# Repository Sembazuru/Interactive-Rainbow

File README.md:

# Interactive-Rainbow
Interactive Rainbow panel of RGB LEDs for the Barrel of Makers windmill project.

This is the state as first built as the Trippy-RGB wall with point-to-point wiring.
Any updates or changes to the first build should be documented here.

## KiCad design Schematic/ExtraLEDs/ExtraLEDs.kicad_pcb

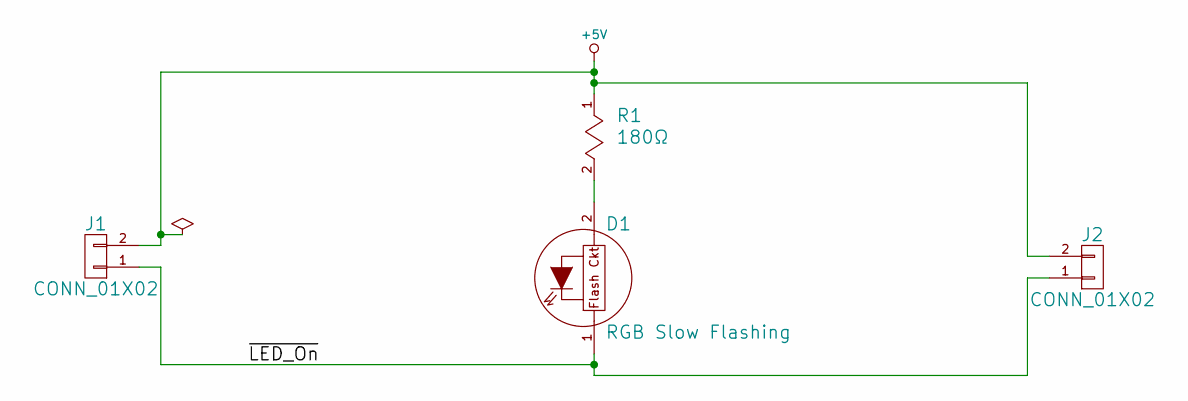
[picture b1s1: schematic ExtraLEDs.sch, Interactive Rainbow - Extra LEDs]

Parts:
D1: RGB Slow Flashing; LEDRD254W50D500H960P; MfgPart ADA679
J1, J2: CONN_01X02; HDRV2W64P254_1X2_508X254X1016A
R1: 180Ω; RESAD1016W56L681D259

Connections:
+5V: J1.2, J2.2, R1.1
/~LED_On: D1.1 (K), J1.1, J2.1
unnamed: D1.2 (A), R1.2

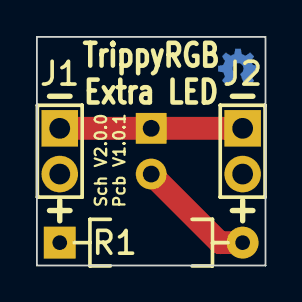
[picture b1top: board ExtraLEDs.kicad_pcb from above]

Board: 2 copper layers, 12.7 x 12.7 mm, 4 parts (1 on the bottom side), 3 nets.

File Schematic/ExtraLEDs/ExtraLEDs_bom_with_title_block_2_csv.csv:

Source,C:\Users\Chris\Google Drive\Barrel of Makers\Windmill LED panel\Schematic\ExtraLEDs\ExtraLEDs.sch
Kicad Rev,Eeschema 4.0.4-stable
Generated Date,2016-10-07 00:31:17

Title,Interactive Rainbow
Company,Sembazuru Circuit (for Barrel of Makers)
Revision,2.0.0
Date Issue,2016-05-27
Comment,2.0.0 Split schematic up for 4 individual PWB designs

Reference,Value,CommonPartLibrary,MFN,MFP,Package ID,S1PN,S1PL,S2PN,S2PL,Characteristics,Description,Critical,Source,Notes,Mfg,MfgPart,Library,Library Ref
D1,RGB Slow Flashing,CPL-LED-RGB-CYCLING-SLOW*,AdaFruit,679,JEDEC footprint name,ADA679,https://octopart.com/search?q=ADA679,679,https://www.adafruit.com/product/679,Diffused 5mm Slow Fade Flashing RGB LED - 10 pack,Self-cycling LED, slow speed, 10pk,Y,SPEC,Explain critera for "ANY" Source,AdaFruit,ADA679,NewUnsorted,LED_Flashing
R1,180Ω,CPL-RES-THT-180-0.25W*,Yageo,MFR-25FBF52-180R,JEDEC footprint name,MFR-25FBF52-180R,https://octopart.com/search?q=MFR-25FBF52-180R,603-MFR-25FBF52-180R,http://www.mouser.com/search/ProductDetail.aspx?R=0virtualke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,180Ω,Current limiting resistor for LED.,N,ANY,Any tolerance THT 180Ω 1/4W or 1/8W resistor will do.,,,NewUnsorted,RES
J1,CONN_01X02,CPL-,Manufacturer Name,Manufacturer Part Number,JEDEC footprint name,Source1 Part Number,Source1 Product Link,Source2 Part Number,Source2 Product Link,Voltage / Current / Tolerance / Ect specs,Footprint for 25mil square pin header. Use header or direct solder wires.,Y / N,ANY / SPEC,Explain critera for "ANY" Source,,,NewUnsorted,CONN_01X02
J2,CONN_01X02,CPL-,Manufacturer Name,Manufacturer Part Number,JEDEC footprint name,Source1 Part Number,Source1 Product Link,Source2 Part Number,Source2 Product Link,Voltage / Current / Tolerance / Ect specs,Footprint for 25mil square pin header. Use header or direct solder wires.,Y / N,ANY / SPEC,Explain critera for "ANY" Source,,,NewUnsorted,CONN_01X02

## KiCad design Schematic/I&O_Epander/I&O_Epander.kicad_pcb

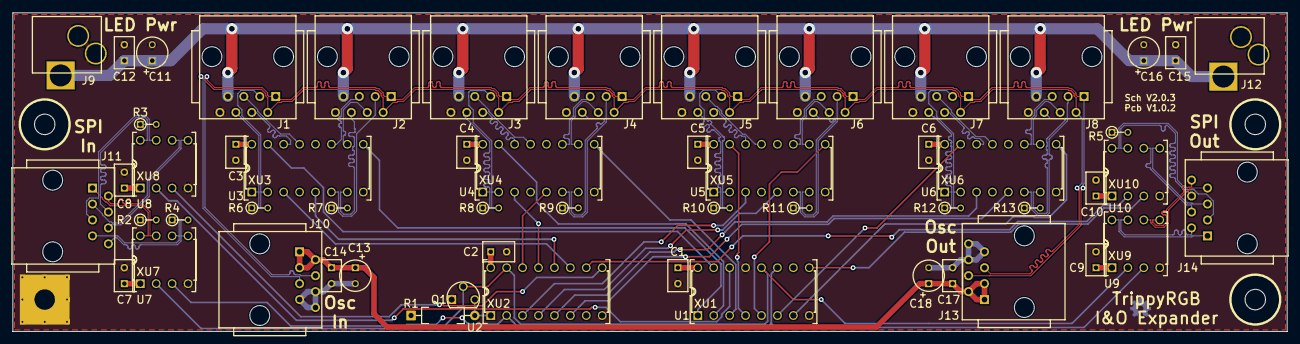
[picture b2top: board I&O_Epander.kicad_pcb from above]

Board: 2 copper layers, 203.2 x 50.8 mm, 70 parts (0 on the bottom side), 76 nets.

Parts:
C1, C2, C3, C4, C5, C6, C7, C8, C9, C10, C12, C14, C15, C17: 0.1µF; CAPRR254W51L508T318H660P
C11, C13, C16, C18: 10µF; CAPPRD254W50D500H850
J1, J2, J3, J4, J5, J6, J7, J8, J10, J11, J13, J14: RJ45-Unshielded; WURTH_615008144221
J9, J12: KLDVHCX-0202-A; KYCON_KLDVHCX-0202-x_CirHole
MH1: #4 PTH; MTGP794H326V8P
MH2, MH3, MH4: #4 NPTH; MTGNP794H326Z794P
Q1: VN3205; TO92184P520H734-3
R1: 1kΩ; RESAD1016W56L681D259
R2, R3, R4, R5, R6, R7, R8, R9, R10, R11, R12, R13: 100Ω; RESADV254W45L350D185
U1: 74HC595; DIPS762W45P254L2019H508Q16
U2: 74HC165; DIPS762W45P254L2019H508Q16
U3, U4, U5, U6: 75C1168; DIPS762W45P254L2019H508Q16
U7: uA9637AC; DIPS762W45P254L1003H508Q8
U8, U10: DS8921; DIPS762W45P254L1003H508Q8
U9: uA9638C; DIPS762W45P254L1003H508Q8
XU1, XU2, XU3, XU4, XU5, XU6: IC_Socket16; DIPfS794W45P254L1969H508Q16
XU7, XU8, XU9, XU10: IC_Socket08; DIPfS762W45P254L1016H508Q8

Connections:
+5V(1): C1.1, C2.1, C3.1, C4.1, C5.1, C6.1, C7.1, C8.1, C9.1, C10.1, C13.1, C14.1, C17.1, C18.1, J10.1, J10.2, J10.3, J13.1, J13.2, J13.3, R1.1, U1.10, U1.16, U2.16, U3.4, U3.12, U3.16, U4.4, U4.12, U4.16, U5.4, U5.12, U5.16, U6.4, U6.12, U6.16, U7.1, U8.1, U9.1, U10.1
+5V(2): C11.1, C12.1, C15.1, C16.1, J1.7, J2.7, J3.7, J4.7, J5.7, J6.7, J7.7, J8.7, J9.1, J12.1
/In1: U2.11, U3.3
/In1+: J1.3, R6.2, U3.2
/In1-: J1.6, R6.1, U3.1
/In2: U2.12, U3.5
/In2+: J2.3, R7.1, U3.6
/In2-: J2.6, R7.2, U3.7
/In3: U2.13, U4.3
/In3+: J3.3, R8.2, U4.2
/In3-: J3.6, R8.1, U4.1
/In4: U2.14, U4.5
/In4+: J4.3, R9.1, U4.6
/In4-: J4.6, R9.2, U4.7
/In5: U2.3, U5.3
/In5+: J5.3, R10.2, U5.2
/In5-: J5.6, R10.1, U5.1
/In6: U2.4, U5.5
/In6+: J6.3, R11.1, U5.6
/In6-: J6.6, R11.2, U5.7
/In7: U2.5, U6.3
/In7+: J7.3, R12.2, U6.2
/In7-: J7.6, R12.1, U6.1
/In8: U2.6, U6.5
/In8+: J8.3, R13.1, U6.6
/In8-: J8.6, R13.2, U6.7
/MISO: U2.9, U8.3
/MISO': U2.10, U10.2
/MISO'+: J14.3, R5.1, U10.8
/MISO'-: J14.6, R5.2, U10.7
/MISO+: J11.3, U8.6
/MISO-: J11.6, U8.5
/MOSI: U1.14, U8.2
/MOSI': U1.9, U10.3
/MOSI'+: J14.4, U10.6
/MOSI'-: J14.5, U10.5
/MOSI+: J11.4, R3.1, U8.8
/MOSI-: J11.5, R3.2, U8.7
/Out1: U1.15, U3.15
/Out1+: J1.4, U3.14
/Out1-: J1.5, U3.13
/Out2: U1.1, U3.9
/Out2+: J2.4, U3.10
/Out2-: J2.5, U3.11
/Out3: U1.2, U4.15
/Out3+: J3.4, U4.14
/Out3-: J3.5, U4.13
/Out4: U1.3, U4.9
/Out4+: J4.4, U4.10
/Out4-: J4.5, U4.11
/Out5: U1.4, U5.15
/Out5+: J5.4, U5.14
/Out5-: J5.5, U5.13
/Out6: U1.5, U5.9
/Out6+: J6.4, U5.10
/Out6-: J6.5, U5.11
/Out7: U1.6, U6.15
/Out7+: J7.4, U6.14
/Out7-: J7.5, U6.13
/Out8: U1.7, U6.9
/Out8+: J8.4, U6.10
/Out8-: J8.5, U6.11
/SCK: U1.11, U2.2, U7.3, U9.3
/SCK'+: J14.7, U9.6
/SCK'-: J14.8, U9.5
/SCK+: J11.7, R4.1, U7.6
/SCK-: J11.8, R4.2, U7.5
/SS: Q1.3, R1.2, U2.1
/~IR_Osc+: J1.1, J2.1, J3.1, J4.1, J5.1, J6.1, J7.1, J8.1, J10.4, J13.4
/~IR_Osc-: J1.2, J2.2, J3.2, J4.2, J5.2, J6.2, J7.2, J8.2, J10.5, J13.5
/~SS: Q1.2, U1.12, U2.15, U7.2, U9.2
/~SS'+: J14.1, U9.8
/~SS'-: J14.2, U9.7
/~SS+: J11.1, R2.1, U7.8
/~SS-: J11.2, R2.2, U7.7
GND: C1.2, C2.2, C3.2, C4.2, C5.2, C6.2, C7.2, C8.2, C9.2, C10.2, C11.2, C12.2, C13.2, C14.2, C15.2, C16.2, C17.2, C18.2, J1.8, J2.8, J3.8, J4.8, J5.8, J6.8, J7.8, J8.8, J9.2, J9.3, J10.6, J10.7, J10.8, J12.2, J12.3, J13.6, J13.7, J13.8, MH1.0, Q1.1, U1.8, U1.13, U2.8, U3.8, U4.8, U5.8, U6.8, U7.4, U8.4, U9.4, U10.4

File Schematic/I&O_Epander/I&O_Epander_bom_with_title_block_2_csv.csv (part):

Source,C:/Users/Chris/Google Drive/Barrel of Makers/Windmill LED panel/Schematic/I&O_Epander/I&O_Epander.sch
Kicad Rev,Eeschema 4.0.5
Generated Date,2017-01-30 23:01:14

Title,Interactive Rainbow
Company,Sembazuru Circuits (for Barrel of Makers)
Revision,2.0.2
Date Issue,2017-01-19
Comment,2.0.0 Split schematic up for 4 individual PWB designs
Comment,2.0.1 Implement differential signalling for inter-board communication.
Comment,2.0.2 Add termination resistors for differential inputs.

"Reference","Value","CommonPartLibrary","MFN","MFP","Package ID","S1PN","S1PL","S2PN","S2PL","Characteristics","Description","Critical","Source","Notes","Library","Library Ref"
"C1","0.1µF","CPL-CAP-X7R-THT-100NF-50V","Kemet","C320C104K5R5TA","JEDEC footprint name","C320C104K5R5TA","https://octopart.com/c320c104k5r5ta-kemet-39420400","80-C320C104K5R","http://www.mouser.com/search/ProductDetail.aspx?R=0virtualke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","Capacitor / Ceramic / 0.1µF / 48WVDC(min.)","IC Bypass.","N","ANY","ANY X7R 0.1µF capacitor 0.1" pitch","NewUnsorted","CAP_NP"
"U1","74HC595","CPL-DIC-SHIFTREG-SER-PAR","Texas Instruments","SN74HC595N","PDIP16","SN74HC595N","https://octopart.com/sn74hc595n-texas+instruments-19771","SN74HC595N","https://store.ti.com/SN74HC595N.aspx","+5VDC logic / 16Pin Dip","Serial to parallel converter. Recieved MISO and controls LEDs.","Y","ANY","Any 74xx595 or direct replacement, 5V TTL/CMOS compatible.","NewUnsorted","74HC595"
"U2","74HC165","CPL-DIC-SHIFTREG-PAR-SER","Texas Instruments","SN74HC165N","PDIP16","SN74HC165N","https://octopart.com/sn74hc165n-texas+instruments-13591","SN74HC165N","https://store.ti.com/SN74HC165N.aspx","+5VDC logic / 16Pin Dip","Parallel to serial converter. Recieve sensor states and send to the µC via MOSI.","Y","ANY","Any 74xx165 or direct replacement, 5V TTL/CMOS compatible.","NewUnsorted","74HC165"
"R1","1kΩ","CPL-RES-THT-1K-0.25W","Yageo","MFR-25FBF52-1K","JEDEC footprint name","MFR-25FBF52-1K","https://octopart.com/mfr-25fbf52-1k-yageo-18902051","603-MFR-25FBF52-1K","http://www.mouser.com/search/ProductDetail.aspx?R=0virtualke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","1kΩ","Biasing/pull-up resistor for Q1 inverter.","N","ANY","Any tolerance THT 1kΩ 1/4W or 1/8W resistor will do.","NewUnsorted","RES"
"Q1","VN3205","CPL-TRN-NFET-50V-1.2A-THT*","Microchip Technology","VN3205N3-G","TO-92","VN3205N3-G","https://octopart.com/vn3205n3-g-microchip-47153678","689-VN3205N3-G","http://www.mouser.com/search/ProductDetail.aspx?R=0virtualke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","MOSFET N-Channel / 50Vds / 1.2A / 1W","SS Signal inverter.","Y","ANY","Any TO-92 N-MOSFET SGD pin configuration >1A","NewUnsorted","Q_NMOS_SGD"
"J1","RJ45-Unshielded","CPL-CON-ETHERNET-VERTICAL*","Wurth Electronics","615008144221","JEDEC footprint name","615008144221","https://octopart.com/615008144221-w%C3%BCrth+elektronik-19991165","710-615008144221","http://www.mouser.com/search/ProductDetail.aspx?R=0virtualke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","CONN MOD JACK 8P8C VERT UNSHLD","Power and signal connector for LED&Sensor board 1.","Y","SPEC","Explain critera for "ANY" Source","NewUnsorted","RJ45-Unshielded"
"J9","KLDVHCX-0202-A","CPL-CON-BARREL-2.1MM-VERT*","Kycon","KLDVHCX-0202-A","JEDEC footprint name","KLDVHCX-0202-A","https://octopart.com/kldvhcx-0202-a-kycon-21628247","806-KLDVHCX-0202-A","http://www.mouser.com/search/ProductDetail.aspx?R=0virtualke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","12V DC / 5A / Tolerance / Ect specs","LED&Sensor board power input.","Y","SPEC","Connectors footprints are part specific.","NewUnsorted","JACK-PWR"
"U3","75C1168","CPL-IIC-DIFFERENTIAL-DRIVER-RECEIVER-DUAL*","Texas Instruments","SN75C1168N","PDIP16","SN75C1168N","https://octopart.com/sn75c1168n-texas+instruments-503774","595-SN75C1168N","http://www.mouser.com/search/ProductDetail.aspx?R=0virtualke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","+5VDC logic / 16Pin Dip","Differential driver/receiver for communication over twisted pair.","Y","ANY","Any 75xx1168 or direct replacement, 5V TTL/CMOS compatible.","NewUnsorted","75C1168"
"U7","uA9637AC","CPL-IIC-DIFFERENTIAL-RECEIVER-DUAL*","Texas Instruments","UA9637ACP","PDIP8","UA9637ACP","https://octopart.com/ua9637acp-texas+instruments-503687","UA9637ACP","https://store.ti.com/UA9637ACP.aspx","+5VDC logic / 8Pin Dip","Differential receiver for communication over twisted pair.","Y","ANY","Any UA9637 direct replacement, 5V TTL/CMOS compatible.","NewUnsorted","uA9637AC"
"U9","uA9638C","CPL-IIC-DIFFERENTIAL-DRIVER-DUAL*","Texas Instruments","UA9638CP","PDIP8","UA9638CP","https://octopart.com/ua9638cp-texas+instruments-503688","UA9638CP","https://store.ti.com/UA9638CP.aspx","+5VDC logic / 8Pin Dip","Differential driver for communication over twisted pair.","Y","ANY","Any uA9638C direct replacement, 5V TTL/CMOS compatible.","NewUnsorted","uA9638C"
"XU1","IC_Socket16","CPL-","3M","4816-3004-CP","JEDEC footprint name","4816-3004-CP","https://octopart.com/4816-3004-cp-3m-767151","517-4816-3004-CP","http://www.mouser.com/search/ProductDetail.aspx?R=0virtualke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","16pin, 0.1” pitch, 0.3” wide, DIP","IC Socket.","N","ANY","any 16pin 0.1"pitch 0.3"width socket.","NewUnsorted","IC_Socket16"
"XU7","IC_Socket08","CPL-","3M","4808-3004-CP","PDIP8","4808-3004-CP","https://octopart.com/4808-3004-cp-3m-767259","517-4808-3004-CP","http://www.mouser.com/search/ProductDetail.aspx?R=0virtualke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","8pin, 0.1” pitch, 0.3” wide, DIP","IC Socket.","N","ANY","Any 8pin 0.1"pitch 0.3"width socket.","NewUnsorted","IC_Socket08"
"C11","10µF","CPL-CAP-TANT-THT-10UF-50V","AVX","TAP106K050SCS","JEDEC footprint name","TAP106K050SCS","https://octopart.com/tap106k050scs-avx-9633","581-TAP106K050SCS","Source2 Product Link","1µF / Tantalum / 10% / 50WVDC","Power noise filter.","N","ANY","Roughly 10µF minimum 15WVDC","NewUnsorted","CAP_P"
"MH1","#4 PTH","CPL-","Manufacturer Name","Manufacturer Part Number","JEDEC footprint name","Source1 Part Number","Source1 Product Link","Source2 Part Number","Source2 Product Link","#4 Machine screw size","Mounting hole with ground connection.","Y / N","ANY / SPEC","Explain critera for "ANY" Source","NewUnsorted","MOUNTING_HOLE_PTH"
"MH2","#4 NPTH","CPL-","Manufacturer Name","Manufacturer Part Number","JEDEC footprint name","Source1 Part Number","Source1 Product Link","Source2 Part Number","Source2 Product Link","#4 Machine screw size","Mounting hole, electrically isolated.","Y / N","ANY / SPEC","Explain critera for "ANY" Source","NewUnsorted","MOUNTING_HOLE_NPTH"
"J2","RJ45-Unshielded","CPL-CON-ETHERNET-VERTICAL*","Wurth Electronics","615008144221","JEDEC footprint name","615008144221","https://octopart.com/615008144221-w%C3%BCrth+elektronik-19991165","710-615008144221","http://www.mouser.com/search/ProductDetail.aspx?R=0virtualke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","CONN MOD JACK 8P8C VERT UNSHLD","Power and signal connector for LED&Sensor board 2.","Y","SPEC","Explain critera for "ANY" Source","NewUnsorted","RJ45-Unshielded"
"J3","RJ45-Unshielded","CPL-CON-ETHERNET-VERTICAL*","Wurth Electronics","615008144221","JEDEC footprint name","615008144221","https://octopart.com/615008144221-w%C3%BCrth+elektronik-19991165","710-615008144221","http://www.mouser.com/search/ProductDetail.aspx?R=0virtualke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","CONN MOD JACK 8P8C VERT UNSHLD","Power and signal connector for LED&Sensor board 3.","Y","SPEC","Explain critera for "ANY" Source","NewUnsorted","RJ45-Unshielded"
"J4","RJ45-Unshielded","CPL-CON-ETHERNET-VERTICAL*","Wurth Electronics","615008144221","JEDEC footprint name","615008144221","https://octopart.com/615008144221-w%C3%BCrth+elektronik-19991165","710-615008144221","http://www.mouser.com/search/ProductDetail.aspx?R=0virtualke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","CONN MOD JACK 8P8C VERT UNSHLD","Power and signal connector for LED&Sensor board 4.","Y","SPEC","Explain critera for "ANY" Source","NewUnsorted","RJ45-Unshielded"
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
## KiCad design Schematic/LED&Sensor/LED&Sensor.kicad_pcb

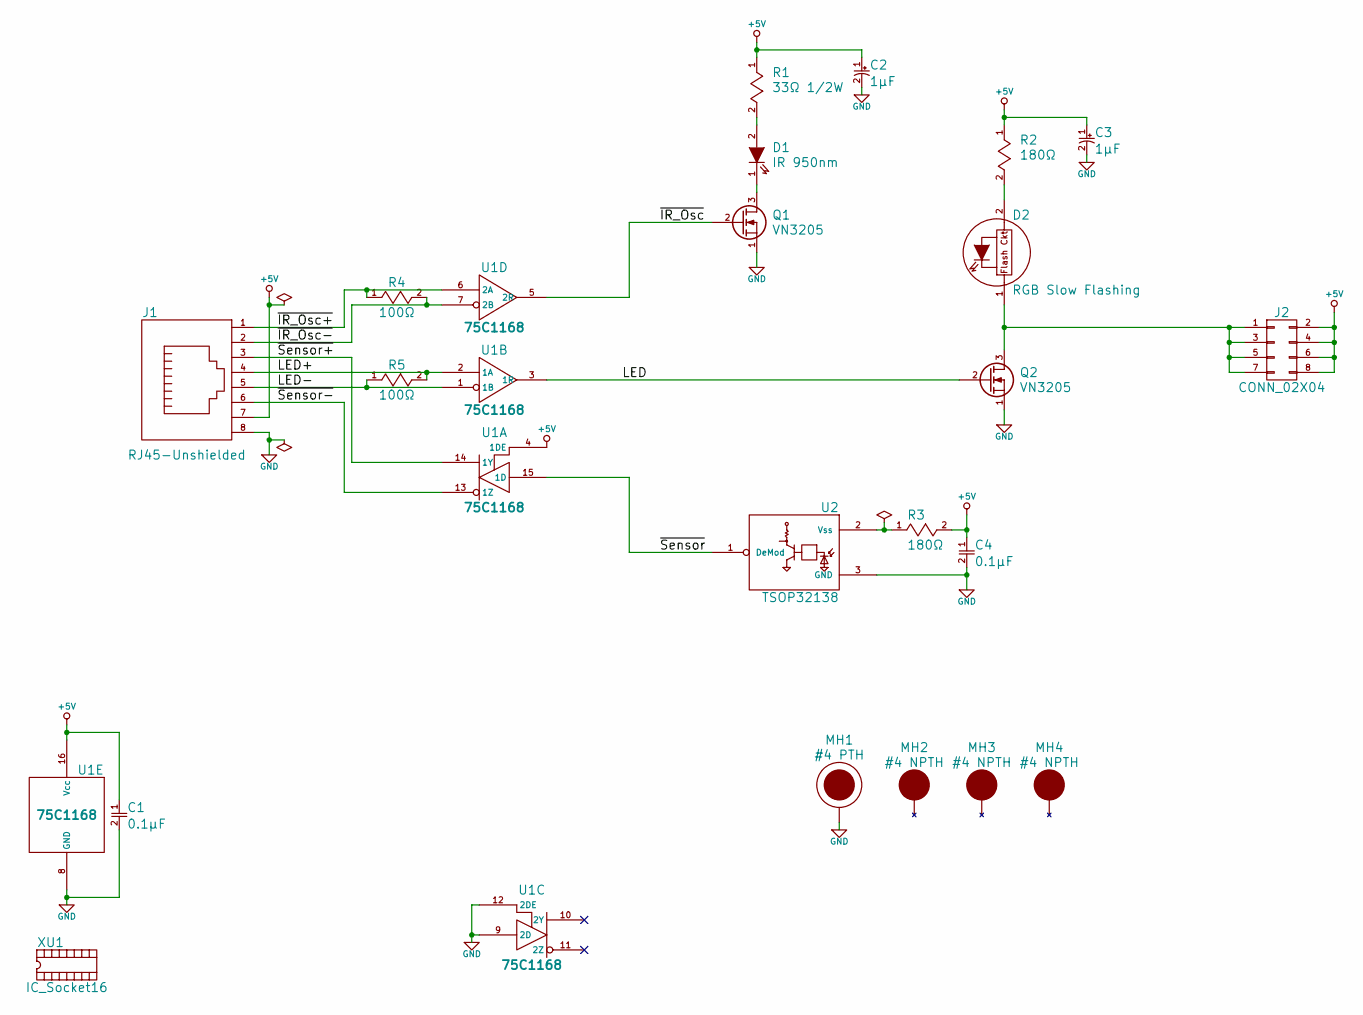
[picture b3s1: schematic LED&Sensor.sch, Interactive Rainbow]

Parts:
C1, C4: 0.1µF; CAPRR254W51L508T318H660P
C2, C3: 1µF; CAPPRD254W50D500H850
D1: IR 950nm; LEDRD254W50D500H960P
D2: RGB Slow Flashing; LEDRD254W50D500H960P
J1: RJ45-Unshielded; WURTH_615008144221
J2: CONN_02X04; Pin_Header_Straight_2x04
MH1: #4 PTH; MTGP794H326V8P
MH2, MH3, MH4: #4 NPTH; MTGNP794H326Z794P
Q1, Q2: VN3205; TO92184P520H734-3
R1: 33Ω 1/2W; RESAD1270W60L900D323
R2, R3: 180Ω; RESAD1016W56L681D259
R4, R5: 100Ω; RESADV254W45L350D185
U1: 75C1168; DIPS762W45P254L2019H508Q16
U2: TSOP32138; TO_VISHAY_TSOP3nnnnn
XU1: IC_Socket16; DIPfS794W45P254L1969H508Q16

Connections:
+5V: C1.1, C2.1, C3.1, C4.1, J1.7, J2.2, J2.4, J2.6, J2.8, R1.1, R2.1, R3.2, U1.4 (1DE), U1.16 (Vcc)
/LED: Q2.2 (G), U1.3 (1R)
/LED+: J1.4, R5.2, U1.2 (1A)
/LED-: J1.5, R5.1, U1.1 (1B)
/~IR_Osc: Q1.2 (G), U1.5 (2R)
/~IR_Osc+: J1.1, R4.1, U1.6 (2A)
/~IR_Osc-: J1.2, R4.2, U1.7 (2B)
/~Sensor: U1.15 (1D), U2.1 (DeMod)
/~Sensor+: J1.3, U1.14 (1Y)
/~Sensor-: J1.6, U1.13 (1Z)
GND: C1.2, C2.2, C3.2, C4.2, J1.8, MH1.0, Q1.1 (S), Q2.1 (S), U1.8 (GND), U1.9 (2D), U1.12 (2DE), U2.3 (GND)
unnamed: D1.1 (K), Q1.3 (D)
unnamed: D1.2 (A), R1.2
unnamed: D2.1 (K), J2.1, J2.3, J2.5, J2.7, Q2.3 (D)
unnamed: D2.2 (A), R2.2
unnamed: R3.1, U2.2 (Vss)

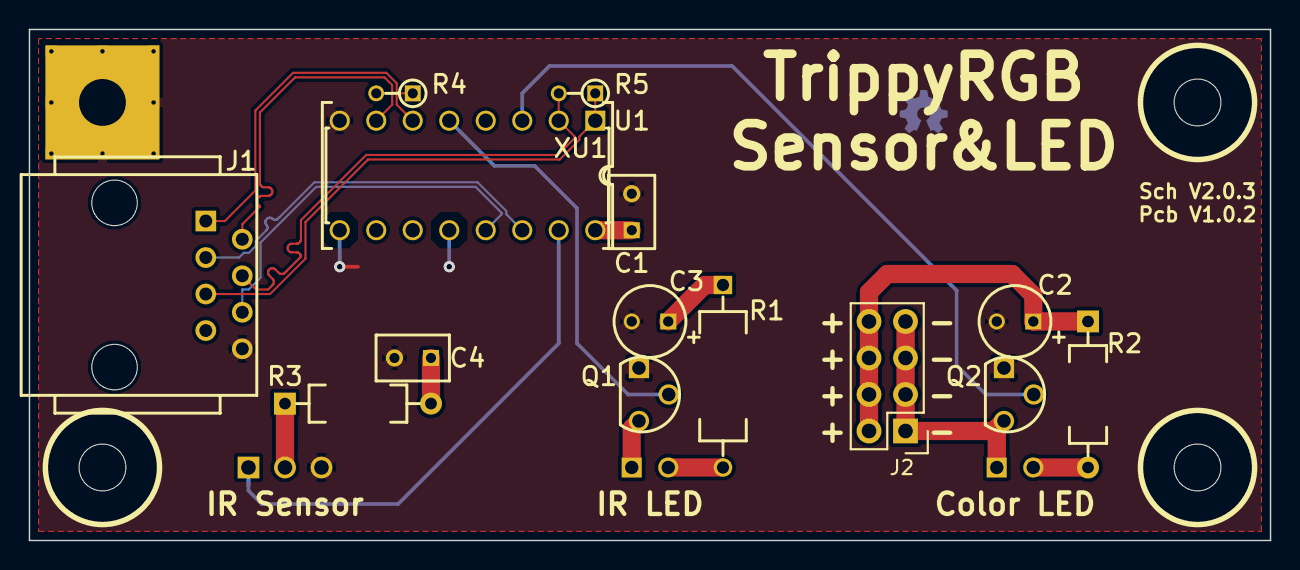
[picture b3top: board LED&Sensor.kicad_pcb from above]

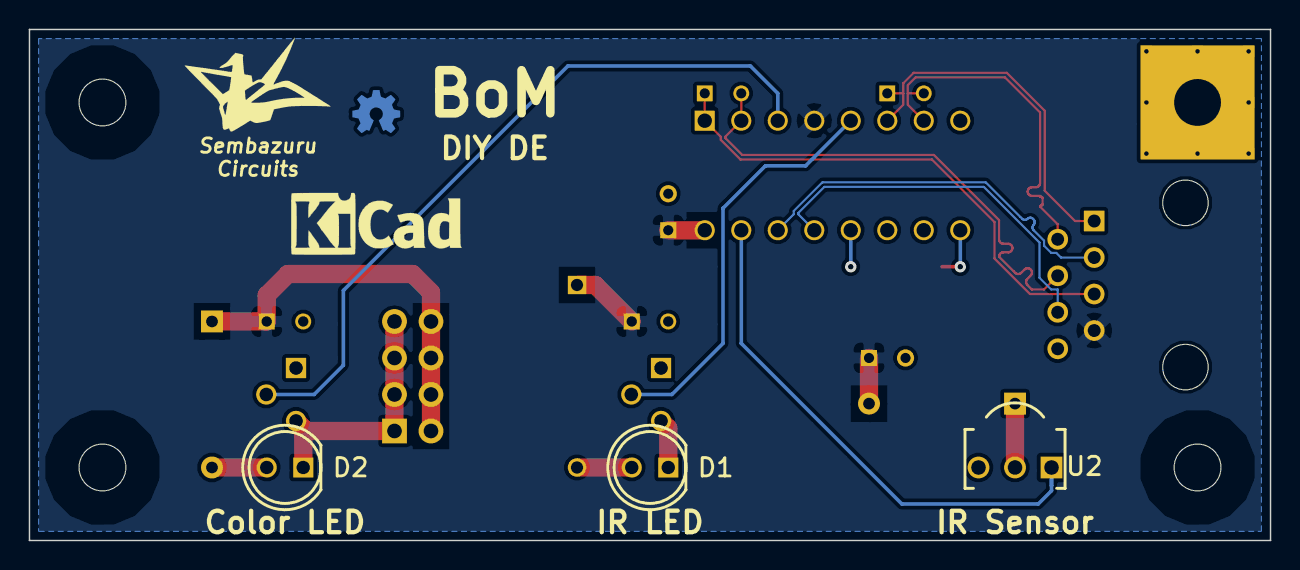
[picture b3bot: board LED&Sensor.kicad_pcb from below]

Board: 2 copper layers, 86.4 x 35.6 mm, 22 parts (3 on the bottom side), 16 nets.

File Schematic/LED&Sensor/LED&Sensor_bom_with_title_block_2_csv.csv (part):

Source,C:/Users/Chris/Google Drive/Barrel of Makers/Windmill LED panel/Schematic/LED&Sensor/LED&Sensor.sch
Kicad Rev,Eeschema 4.0.5
Generated Date,2017-01-20 00:39:38

Title,Interactive Rainbow
Company,Sembazuru Circuit (for Barrel of Makers)
Revision,2.0.2
Date Issue,2017-01-20
Comment,2.0.0 Split schematic up for 4 individual PWB designs
Comment,2.0.1 Implement differential signaling for inter-board communications.
Comment,2.0.2 Add termination resistors for differential inputs.

"Reference","Value","CommonPartLibrary","MFN","MFP","Package ID","S1PN","S1PL","S2PN","S2PL","Characteristics","Description","Critical","Source","Notes","Library","Library Ref"
"D1","IR 950nm","CPL-LED-5MM-IR*","Vishay","TSUS5202","JEDEC footprint name","TSUS5202","https://octopart.com/tsus5202-vishay-55401812","78-TSUS5202","http://www.mouser.com/search/ProductDetail.aspx?R=0virtualke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","1.7Vf / 100mA / 950nm / 5mm","IR Emitter.","Y","ANY","950nm 5mm","NewUnsorted","LED"
"U2","TSOP32138","CPL-SEN-IR","Vishay","TSOP32138","JEDEC footprint name","TSOP32138","https://octopart.com/tsop32138-vishay-39643233","782-TSOP32138","http://www.mouser.com/search/ProductDetail.aspx?R=0virtualke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","38kHz / 30kΩ pull-up collector output / AGC1 / OUT-Vs-GND pin order","38kHz remote reciever. Looking for reflected light from D2.","Y","SPEC","Explain critera for "ANY" Source","NewUnsorted","TSOP321xx"
"R3","180Ω","CPL-RES-THT-180-0.25W*","Yageo","MFR-25FBF52-180R","JEDEC footprint name","MFR-25FBF52-180R","https://octopart.com/search?q=MFR-25FBF52-180R","603-MFR-25FBF52-180R","http://www.mouser.com/search/ProductDetail.aspx?R=0virtualke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","33Ω to 1kΩ","EOS protection for sensor.","N","ANY","Any tolerance THT 33Ω to 1kΩ 1/4W or 1/8W resistor will do.","NewUnsorted","RES"
"C4","0.1µF","CPL-CAP-X7R-THT-100NF-50V","Kemet","C320C104K5R5TA","JEDEC footprint name","C320C104K5R5TA","https://octopart.com/c320c104k5r5ta-kemet-39420400","80-C320C104K5R","http://www.mouser.com/search/ProductDetail.aspx?R=0virtualke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","Capacitor / Ceramic / 0.1µF / 48WVDC(min.)","EOS protection for sensor.","Y / N","ANY","Any monolithic ceramic cap >= 0.1µF.","NewUnsorted","CAP_NP"
"D2","RGB Slow Flashing","CPL-LED-RGB-CYCLING-SLOW*","AdaFruit","ADA679","JEDEC footprint name","ADA679","https://octopart.com/679-adafruit+industries-32978805","679","https://www.adafruit.com/product/679","3.4Vf / 20mA / Tolerance / Ect specs","Color changing LED. (AdaFruit 1qty = 10pcs)","Y","ANY","Explain critera for "ANY" Source","NewUnsorted","LED_Flashing"
"J1","RJ45-Unshielded","CPL-CON-ETHERNET-VERTICAL*","Wurth Electronics","615008144221","JEDEC footprint name","615008144221","https://octopart.com/615008144221-w%C3%BCrth+elektronik-19991165","710-615008144221","http://www.mouser.com/search/ProductDetail.aspx?R=0virtualke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","CONN MOD JACK 8P8C VERT UNSHLD","Power and signal connector.","Y","SPEC","Explain critera for "ANY" Source","NewUnsorted","RJ45-Unshielded"
"J2","CONN_02X04","CPL-HDR-MALE-2ROW-8POS*","Amphenol FCI","68602-408HLF","JEDEC footprint name","68602-408HLF","https://octopart.com/68602-408hlf-fci-40410180","649-68602-408HLF","http://www.mouser.com/search/ProductDetail.aspx?R=0virtualke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","Straight, 0.1" pitch, 2-row 4-column (8 position), 25mil square pin","Connection to Extra LEDs.","Y / N","ANY","Bergstick or compatible","NewUnsorted","CONN_02X04"
"Q1","VN3205","CPL-TRN-NFET-50V-1.2A-THT*","Microchip Technology","VN3205N3-G","TO-92","VN3205N3-G","https://octopart.com/vn3205n3-g-microchip-47153678","689-VN3205N3-G","http://www.mouser.com/search/ProductDetail.aspx?R=0virtualke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","MOSFET N-Channel / 50Vds / 1.2A / 1W","LED switch.","Y","ANY","Any TO-92 N-MOSFET SGD pin configuration >1A","NewUnsorted","Q_NMOS_SGD"
"U1","75C1168","CPL-IIC-DIFFERENTIAL-DRIVER-RECEIVER-DUAL*","Texas Instruments","SN75C1168N","PDIP16","SN75C1168N","https://octopart.com/sn75c1168n-texas+instruments-503774","595-SN75C1168N","http://www.mouser.com/search/ProductDetail.aspx?R=0virtualke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","+5VDC logic / 16Pin Dip","Differential driver/receiver for communication over twisted pair.","Y","ANY","Any 75xx1168 or direct replacement, 5V TTL/CMOS compatible..","NewUnsorted","75C1168"
"MH1","#4 PTH","CPL-","Manufacturer Name","Manufacturer Part Number","JEDEC footprint name","Source1 Part Number","Source1 Product Link","Source2 Part Number","Source2 Product Link","#4 Machine screw size","Mounting hole with ground connection.","Y / N","ANY / SPEC","Explain critera for "ANY" Source","NewUnsorted","MOUNTING_HOLE_PTH"
"MH2","#4 NPTH","CPL-","Manufacturer Name","Manufacturer Part Number","JEDEC footprint name","Source1 Part Number","Source1 Product Link","Source2 Part Number","Source2 Product Link","#4 Machine screw size","Mounting hole, electrically isolated.","Y / N","ANY / SPEC","Explain critera for "ANY" Source","NewUnsorted","MOUNTING_HOLE_NPTH"
"XU1","IC_Socket16","CPL-","3M","4816-3004-CP","JEDEC footprint name","4816-3004-CP","https://octopart.com/4816-3004-cp-3m-767151","517-4816-3004-CP","http://www.mouser.com/search/ProductDetail.aspx?R=0virtualke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","16pin, 0.1” pitch, 0.3” wide, DIP","IC Socket.","N","ANY","any 16pin 0.1"pitch 0.3"width socket.","NewUnsorted","IC_Socket16"
"R1","33Ω 1/2W","CPL-RES-THT-33-0.5W*","Yageo","MFR50SFTE52-33R","JEDEC footprint name","MFR-25FBF52-180R","https://octopart.com/mfr50sfte52-33r-yageo-29199231","603-MFR50SFTE52-33R","http://www.mouser.com/search/ProductDetail.aspx?R=0virtualke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","33Ω 1/2W","Current limiting resistor for LED.","N","ANY","Any tolerance THT 33Ω 1/2W","NewUnsorted","RES"
"R2","180Ω","CPL-RES-THT-180-0.25W*","Yageo","MFR-25FBF52-180R","JEDEC footprint name","MFR-25FBF52-180R","https://octopart.com/search?q=MFR-25FBF52-180R","603-MFR-25FBF52-180R","http://www.mouser.com/search/ProductDetail.aspx?R=0virtualke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","180Ω","Current limiting resistor for LED.","N","ANY","Any tolerance THT 180Ω 1/4W or 1/8W resistor will do.","NewUnsorted","RES"
"Q2","VN3205","CPL-TRN-NFET-50V-1.2A-THT*","Microchip Technology","VN3205N3-G","TO-92","VN3205N3-G","https://octopart.com/vn3205n3-g-microchip-47153678","689-VN3205N3-G","http://www.mouser.com/search/ProductDetail.aspx?R=0virtualke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","MOSFET N-Channel / 50Vds / 1.2A / 1W","LED switch.","Y","ANY","Any TO-92 N-MOSFET SGD pin configuration >1A","NewUnsorted","Q_NMOS_SGD"
"C1","0.1µF","CPL-CAP-X7R-THT-100NF-50V","Kemet","C320C104K5R5TA","JEDEC footprint name","C320C104K5R5TA","https://octopart.com/c320c104k5r5ta-kemet-39420400","80-C320C104K5R","http://www.mouser.com/search/ProductDetail.aspx?R=0virtualke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","Capacitor / Ceramic / 0.1µF / 48WVDC(min.)","IC Bypass.","Y / N","ANY","ANY X7R 0.1µF capacitor 0.1" pitch","NewUnsorted","CAP_NP"
"MH3","#4 NPTH","CPL-","Manufacturer Name","Manufacturer Part Number","JEDEC footprint name","Source1 Part Number","Source1 Product Link","Source2 Part Number","Source2 Product Link","#4 Machine screw size","Mounting hole"," electrically isolated.","Y / N","ANY / SPEC","Explain critera for "ANY" Source","NewUnsorted","MOUNTING_HOLE_NPTH"
"MH4","#4 NPTH","CPL-","Manufacturer Name","Manufacturer Part Number","JEDEC footprint name","Source1 Part Number","Source1 Product Link","Source2 Part Number","Source2 Product Link","#4 Machine screw size","Mounting hole"," electrically isolated.","Y / N","ANY / SPEC","Explain critera for "ANY" Source","NewUnsorted","MOUNTING_HOLE_NPTH"
"C2","1µF","CPL-CAP-TANT-THT-1UF-50V","AVX","TAP105K050SCS","JEDEC footprint name","TAP105K050SCS","https://octopart.com/tap105k050scs-avx-9445","581-TAP105K050SCS","http://www.mouser.com/search/ProductDetail.aspx?R=0virtualke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","1µF / Tantalum / 10% / 50WVDC","Bypas cap for flashing IR LED.","N","ANY","Roughly 1µF minimum 15WVDC","NewUnsorted","CAP_P"
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
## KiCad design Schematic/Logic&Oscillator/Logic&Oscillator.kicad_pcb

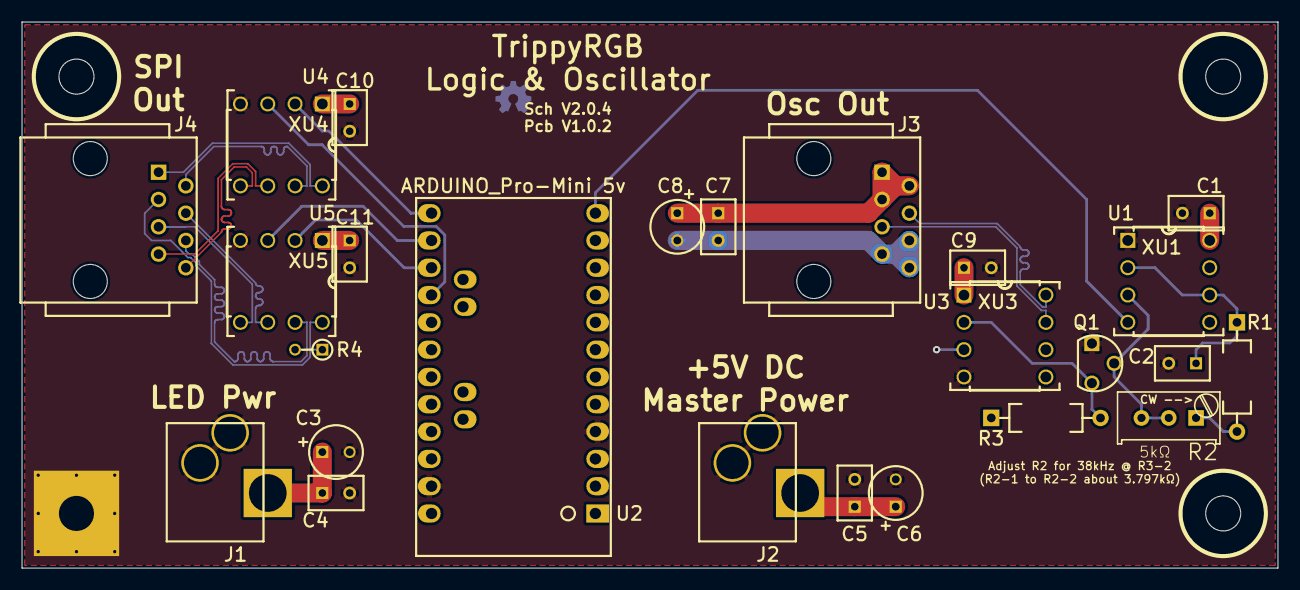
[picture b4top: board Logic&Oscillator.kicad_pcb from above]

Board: 2 copper layers, 116.8 x 50.8 mm, 33 parts (0 on the bottom side), 21 nets.

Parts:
C1, C4, C5, C7, C9, C10, C11: 0.1µF; CAPRR254W51L508T318H660P
C2: 0.001µF; CAPRR254W51L508T318H660P
C3, C6, C8: 10µF; CAPPRD254W50D500H850
J1, J2: KLDVHCX-0202-A; KYCON_KLDVHCX-0202-x_CirHole
J3, J4: RJ45-Unshielded; WURTH_615008144221
MH1: #4 PTH; MTGP794H326V8P
MH2, MH3, MH4: #4 NPTH; MTGNP794H326Z794P
Q1: VN3205; TO92184P520H734-3
R1, R3: 15kΩ; RESAD1016W56L681D259
R2: 5kΩ; TRIM_Bourns3296WA
R4: 100Ω; RESADV254W45L350D185
U1: ICM7555; DIPS762W45P254L1003H508Q8
U2: ARDUINO_Pro-Mini 5v; ARDUINO_Pro-MiniU
U3, U4: uA9638C; DIPS762W45P254L1003H508Q8
U5: DS8921; DIPS762W45P254L1003H508Q8
XU1, XU3, XU4, XU5: IC_Socket08; DIPfS762W45P254L1016H508Q8

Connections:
+5V: C1.1, C3.1, C4.1, C5.1, C6.1, C7.1, C8.1, C9.1, C10.1, C11.1, J1.1, J2.1, J3.1, J3.2, J3.3, R3.1, U1.8, U2.21, U3.1, U4.1, U5.1
/IR_Enable: U1.4, U2.12
/IR_Osc: Q1.2, R2.2, R2.3, U1.3
/MISO: U2.15, U5.2
/MISO+: J4.3, R4.1, U5.8
/MISO-: J4.6, R4.2, U5.7
/MOSI: U2.14, U5.3
/MOSI+: J4.4, U5.6
/MOSI-: J4.5, U5.5
/SCK: U2.16, U4.3
/SCK+: J4.7, U4.6
/SCK-: J4.8, U4.5
/~IR_Osc: Q1.3, R3.2, U3.2
/~IR_Osc+: J3.4, U3.8
/~IR_Osc-: J3.5, U3.7
/~SS: U2.13, U4.2
/~SS+: J4.1, U4.8
/~SS-: J4.2, U4.7
GND: C1.2, C2.2, C3.2, C4.2, C5.2, C6.2, C7.2, C8.2, C9.2, C10.2, C11.2, J1.2, J1.3, J2.2, J2.3, J3.6, J3.7, J3.8, MH1.0, Q1.1, U1.1, U2.4, U2.23, U3.3, U3.4, U4.4, U5.4
unnamed: C2.1, R1.1, U1.2, U1.6
unnamed: R1.2, R2.1

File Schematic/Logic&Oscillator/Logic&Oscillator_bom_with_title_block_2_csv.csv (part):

Source,C:\Users\Chris\Google Drive\Barrel of Makers\Windmill LED panel\Schematic\Logic&Oscillator\Logic&Oscillator.sch
Kicad Rev,Eeschema 4.0.5
Generated Date,2017-01-31 01:27:19

Title,Interactive Rainbow
Company,Sembazuru Circuit (for Barrel of Makers)
Revision,2.0.2
Date Issue,2017-01-31
Comment,2.0.0 Split schematic up for 4 individual PWB designs.
Comment,2.0.1 Impliment differential signalling for inter-board communications.
Comment,2.0.2 Add termination resistors for differential inputs.

"Reference","Value","CommonPartLibrary","MFN","MFP","Package ID","S1PN","S1PL","S2PN","S2PL","Characteristics","Description","Critical","Source","Notes","Mfg","MfgPart","Library","Library Ref"
"U2","ARDUINO_Pro-Mini 5v","CPL-PLT-ARDUINO","SparkFun","DEV-11113","JEDEC footprint name","DEV-11113","https://octopart.com/dev-11113-sparkfun-55832348","DEV-11113","https://www.sparkfun.com/products/11113","5V / 16MHz","Microcontroller Brainbox","Y","SPEC","Explain critera for "ANY" Source","","","Arduino","ARDUINO_Pro-Mini"
"R2","5kΩ","CPL-POT-MULTI-25TURN-5K-0.5W*","Bourns","3296W-1-502LF","JEDEC footprint name","3296W-1-502LF","https://octopart.com/3296w-1-502lf-bourns-69787","652-3296W-1-502LF","http://www.mouser.com/search/ProductDetail.aspx?R=0virtualke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","5kΩ / Multiturn / 0.125W(min)","Timer RC component.","Y","ANY","Any multiturn 5kΩ that will fit Bourns 3296 series footprint.","Bourns","3296W-1-502LF","NewUnsorted","POT_W2"
"J2","KLDVHCX-0202-A","CPL-CON-BARREL-2.1MM-VERT*","Kycon","KLDVHCX-0202-A","JEDEC footprint name","KLDVHCX-0202-A","https://octopart.com/kldvhcx-0202-a-kycon-21628247","806-KLDVHCX-0202-A","http://www.mouser.com/search/ProductDetail.aspx?R=0virtualke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","12V DC / 5A / Tolerance / Ect specs","Master power input.","Y","SPEC","Connectors footprints are part specific.","","","NewUnsorted","JACK-PWR"
"C3","10µF","CPL-CAP-TANT-THT-10UF-50V","AVX","TAP106K050SCS","JEDEC footprint name","TAP106K050SCS","https://octopart.com/tap106k050scs-avx-9633","581-TAP106K050SCS","Source2 Product Link","1µF / Tantalum / 10% / 50WVDC","Power noise filter.","N","ANY","Roughly 10µF minimum 15WVDC","","","NewUnsorted","CAP_P"
"C1","0.1µF","CPL-CAP-X7R-THT-100NF-50V","Kemet","C320C104K5R5TA","JEDEC footprint name","C320C104K5R5TA","https://octopart.com/c320c104k5r5ta-kemet-39420400","80-C320C104K5R","http://www.mouser.com/search/ProductDetail.aspx?R=0virtualke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","Capacitor / Ceramic / 0.1µF / 48WVDC(min.)","IC Bypass.","N","ANY","ANY X7R 0.1µF capacitor 0.1" pitch","","","NewUnsorted","CAP_NP"
"R4","100Ω","CPL-RES-THT-100-0.125W*","Xicon","299-100-RC","JEDEC footprint name","299-100-RC","https://octopart.com/ (Not available)","299-100-RC","http://www.mouser.com/search/ProductDetail.aspx?R=0virtualke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","100Ω Small body","Termination resistor for differential transmission line.","N","ANY","Any tolerance THT 100Ω 1/8W or smaller resistor will do.","","","NewUnsorted","RES"
"Q1","VN3205","CPL-TRN-NFET-50V-1.2A-THT*","Microchip Technology","VN3205N3-G","TO-92","VN3205N3-G","https://octopart.com/vn3205n3-g-microchip-47153678","689-VN3205N3-G","http://www.mouser.com/search/ProductDetail.aspx?R=0virtualke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","MOSFET N-Channel / 50Vds / 1.2A / 1W","Osc inverting buffer.","Y","ANY","Any TO-92 N-MOSFET SGD pin configuration >1A","","","NewUnsorted","Q_NMOS_SGD"
"U1","ICM7555","CPL-LIC-TIMER-7555*","Intersil","ICM7555IPAZ","PDIP8","ICM7555IPAZ","https://octopart.com/icm7555ipaz-intersil-72847","968-ICM7555IPAZ","http://www.mouser.com/search/ProductDetail.aspx?R=0virtualke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","Voltage / Current / Tolerance / Ect specs","38KHz square wave generator.","Y","ANY","Any CMOS 555 variant (7555).","","","NewUnsorted","ICM7555"
"J4","RJ45-Unshielded","CPL-CON-ETHERNET-VERTICAL*","Wurth Electronics","615008144221","JEDEC footprint name","615008144221","https://octopart.com/615008144221-w%C3%BCrth+elektronik-19991165","710-615008144221","http://www.mouser.com/search/ProductDetail.aspx?R=0virtualke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","CONN MOD JACK 8P8C VERT UNSHLD","Power and signal connector for LED&Sensor board 1.","Y","SPEC","Explain critera for "ANY" Source","","","NewUnsorted","RJ45-Unshielded"
"U3","uA9638C","CPL-IIC-DIFFERENTIAL-DRIVER-DUAL*","Texas Instruments","UA9638CP","PDIP8","UA9638CP","https://octopart.com/ua9638cp-texas+instruments-503688","UA9638CP","https://store.ti.com/UA9638CP.aspx","+5VDC logic / 8Pin Dip","Differential driver for communication over twisted pair.","Y","ANY","Any uA9638C direct replacement, 5V TTL/CMOS compatible.","","","NewUnsorted","uA9638C"
"U5","DS8921","CPL-IIC-DIFFERENTIAL-DRIVER-RECEIVER*","Texas Instruments","DS8921N/NOPB","PDIP8","DS8921N/NOPB","https://octopart.com/ds8921n%2Fnopb-texas+instruments-24812137","DS8921N/NOPB","https://store.ti.com/DS8921N/NOPB.aspx","+5VDC logic / 8Pin Dip","Differential driver/receiver for communication over twisted pair.","Y","ANY","Any DS8921 direct replacement, 5V TTL/CMOS compatible.","","","NewUnsorted","DS8921"
"XU1","IC_Socket08","CPL-","3M","4808-3004-CP","PDIP8","4808-3004-CP","https://octopart.com/4808-3004-cp-3m-767259","517-4808-3004-CP","http://www.mouser.com/search/ProductDetail.aspx?R=0virtualke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","8pin, 0.1” pitch, 0.3” wide, DIP","IC Socket.","N","ANY","Any 8pin 0.1"pitch 0.3"width socket.","","","NewUnsorted","IC_Socket08"
"MH2","#4 NPTH","CPL-","Manufacturer Name","Manufacturer Part Number","JEDEC footprint name","Source1 Part Number","Source1 Product Link","Source2 Part Number","Source2 Product Link","#4 Machine screw size","Mounting hole, electrically isolated.","Y / N","ANY / SPEC","Explain critera for "ANY" Source","","","NewUnsorted","MOUNTING_HOLE_NPTH"
"MH1","#4 PTH","CPL-","Manufacturer Name","Manufacturer Part Number","JEDEC footprint name","Source1 Part Number","Source1 Product Link","Source2 Part Number","Source2 Product Link","#4 Machine screw size","Mounting hole with ground connection.","Y / N","ANY / SPEC","Explain critera for "ANY" Source","","","NewUnsorted","MOUNTING_HOLE_PTH"
"J3","RJ45-Unshielded","CPL-CON-ETHERNET-VERTICAL*","Wurth Electronics","615008144221","JEDEC footprint name","615008144221","https://octopart.com/615008144221-w%C3%BCrth+elektronik-19991165","710-615008144221","http://www.mouser.com/search/ProductDetail.aspx?R=0virtualke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","CONN MOD JACK 8P8C VERT UNSHLD","Power and signal connector for LED&Sensor board 1.","Y","SPEC","Explain critera for "ANY" Source","","","NewUnsorted","RJ45-Unshielded"
"U4","uA9638C","CPL-IIC-DIFFERENTIAL-DRIVER-DUAL*","Texas Instruments","UA9638CP","PDIP8","UA9638CP","https://octopart.com/ua9638cp-texas+instruments-503688","UA9638CP","https://store.ti.com/UA9638CP.aspx","+5VDC logic / 8Pin Dip","Differential driver for communication over twisted pair.","Y","ANY","Any uA9638C direct replacement, 5V TTL/CMOS compatible.","","","NewUnsorted","uA9638C"
"XU3","IC_Socket08","CPL-","3M","4808-3004-CP","PDIP8","4808-3004-CP","https://octopart.com/4808-3004-cp-3m-767259","517-4808-3004-CP","http://www.mouser.com/search/ProductDetail.aspx?R=0virtualke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","8pin, 0.1” pitch, 0.3” wide, DIP","IC Socket.","N","ANY","Any 8pin 0.1"pitch 0.3"width socket.","","","NewUnsorted","IC_Socket08"
"XU4","IC_Socket08","CPL-","3M","4808-3004-CP","PDIP8","4808-3004-CP","https://octopart.com/4808-3004-cp-3m-767259","517-4808-3004-CP","http://www.mouser.com/search/ProductDetail.aspx?R=0virtualke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","8pin, 0.1” pitch, 0.3” wide, DIP","IC Socket.","N","ANY","Any 8pin 0.1"pitch 0.3"width socket.","","","NewUnsorted","IC_Socket08"
"XU5","IC_Socket08","CPL-","3M","4808-3004-CP","PDIP8","4808-3004-CP","https://octopart.com/4808-3004-cp-3m-767259","517-4808-3004-CP","http://www.mouser.com/search/ProductDetail.aspx?R=0virtualke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","8pin, 0.1” pitch, 0.3” wide, DIP","IC Socket.","N","ANY","Any 8pin 0.1"pitch 0.3"width socket.","","","NewUnsorted","IC_Socket08"
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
